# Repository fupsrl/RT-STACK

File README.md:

# RT-STACK

**RT-STACK is an open-source, real-time engine-control platform for experimental, motorsport, and bench-development applications.** It combines a deterministic STM32G4 real-time controller with the option to add a Raspberry Pi or another high-level computer for advanced control, data handling, and calibration workflows.

The hardware is deliberately ambitious—twelve injector channels, twelve ignition channels, trigger inputs, lambda interfaces, CAN, and a standard ECU connector—while the checked-in firmware is a transparent, configurable reference implementation. Start on the bench, understand every signal, then adapt the engine, trigger, and output configuration for your application.

> [!WARNING]
> RT-STACK is an engineering/development project. It is not certified, not road-legal, and is supplied without warranty. Do not connect coils, injectors, fuel pumps, or a running engine until you have independently validated the wiring, trigger decode, outputs, and failsafe behaviour on a safe bench setup.

## Why RT-STACK?

- **Real-time where it matters** — the STM32G474 handles time-critical trigger capture, injection and ignition scheduling.
- **Headroom where it helps** — a companion SBC can run high-level logic, graphical control models, logging, and calibration tooling without putting hard real-time output timing at risk.
- **Engine-agnostic by design** — the platform can be adapted for 2-stroke, 4-stroke, Wankel, Diesel, naturally aspirated, or forced-induction projects.
- **A serious hardware base** — the board is designed for high-channel-count PFI/GDI injection, inductive ignition, trigger sensing, lambda control, and general-purpose outputs.
- **Open calibration path** — the wider FUPSRL toolchain supports CAN/XCP workflows and A2L/HEX artefacts for tools such as ETAS INCA and Vector CANape. The current firmware also includes a 500 kbit/s classic-CAN status message and its DBC.

## Architecture

```text
Crank / cam / sensors
        │
        ▼
STM32G474 real-time layer ──► injector, ignition and I/O drivers
        │                         ▲
        ├── CAN telemetry          │ deterministic time-critical control
        ▼                         │
Optional SBC / high-level layer ──┘
  control logic · logging · calibration · user interface
```

The STM32 is the safety- and timing-critical controller. A companion computer is optional and should be treated as a supervisory layer, not as a replacement for deterministic output control.

## Hardware capabilities

| Area | Capability |
| --- | --- |
| Fuel | 12 injector drivers, intended for general-purpose GDI or PFI use; high-voltage DC/DC injector drive and current sensing |
| Ignition | 12 inductive-spark channels |
| Position sensing | 9 general-purpose trigger interfaces for crank, cam, turbo speed, or other timing inputs |
| Lambda | 2 × CJ125 lambda-controller interfaces |
| Outputs | 12 general-purpose outputs with selectable push/pull behaviour |
| Communications | FDCAN-capable MCU; the checked-in project configures classic CAN at 500 kbit/s and includes two UARTs |
| Processor | STM32G474VETx, with analogue comparators and DAC thresholds for injector-drive control |
| Integration | 186-pin standard ECU connector; designed to stack with a Raspberry Pi breakout board for high-level control |

Selected devices include the STM32G474VETx, ACS722 current sensing, CJ125 lambda interfaces, IR2101/TC4427 gate drivers, RGPR30BM40 ignition IGBTs, and IFX007TAUMA1 push/pull drivers. Consult the KiCad design and BOM before making any electrical decision; this README is an overview, not a wiring specification.

## Firmware: current scope

The firmware project lives in [`SW/RT_STACK_V2`](SW/RT_STACK_V2) and is an STM32CubeIDE / STM32CubeMX project. It provides a clear reference structure rather than a sealed, generic binary:

- **Trigger capture and decoding** — trigger edges are timestamped with the DWT cycle counter. The included decoder is configured for a 60-2 crank wheel, optional cam recognition, and 0–720° phase fusion.
- **Engine configuration** — cylinder count, firing order, ignition/injector channel mapping, dwell limit, boost time, and comparator thresholds are centralised in [`engine_config.h`](SW/RT_STACK_V2/Core/Inc/engine_config.h).
- **Trigger configuration** — crank-wheel and cam-pattern settings are centralised in [`trigger_decoder_config.h`](SW/RT_STACK_V2/Core/Inc/trigger_decoder_config.h).
- **Output scheduling** — [`spark.c`](SW/RT_STACK_V2/Core/Src/spark.c) and [`injection.c`](SW/RT_STACK_V2/Core/Src/injection.c) schedule the configured engine channels.
- **Telemetry** — `RT_Status` is sent as an 8-byte classic-CAN frame at identifier `0x100` every 10 ms; [`RT_STACK_V2.dbc`](SW/RT_STACK_V2/RT_STACK_V2.dbc) describes that message.

The committed engine calibration is an **inline-four example** (firing order `1-3-4-2`) and is not a V12 calibration. V12 readiness describes the available I/O architecture; you must supply a correctly validated configuration for every target engine.

## Quick start — safe development workflow

1. Clone the repository and open [`SW/RT_STACK_V2`](SW/RT_STACK_V2) in STM32CubeIDE. The `.ioc` file retains the CubeMX peripheral configuration.
2. Read `engine_config.h` and `trigger_decoder_config.h` before connecting any engine hardware. Configure only a bench-known target first.
3. Build the **Debug** configuration and flash through a correctly wired ST-LINK connection.
4. With injectors and coils disconnected, verify power rails, CAN traffic, trigger-edge polarity, decoded crank angle, RPM, and cam phase using instruments you trust.
5. Validate each output with suitable loads or test fixtures. Add engine actuation only after the whole chain has been checked.

For a guided explanation of the architecture, firmware configuration, CAN telemetry, calibration direction, and bench validation, read the [RT-STACK documentation](https://fupsrl.com/docs/rt-stack-documentation-v1/).

## Repository layout

| Path | Contents |
| --- | --- |
| [`HW`](HW) | KiCad hardware design files |
| [`FAB`](FAB) | Fabrication/manufacturing material |
| [`SW/RT_STACK_V2`](SW/RT_STACK_V2) | STM32CubeIDE firmware project, DBC, source, and CubeMX configuration |
| [`assets`](assets) | Repository artwork, including this README banner |

## Hardware preview

## Calibration and companion tools

RT-STACK is designed to sit within a broader open tooling workflow. The [CM-STACK Simulink Compiler](https://github.com/fupsrl/CM-STACK-Simulink-Compiler) creates deployable generic-Linux applications and calibration artefacts, while [INCAZ](https://github.com/fupsrl/INCAZ) is a lightweight measurement, calibration, and flash client. Treat each integration as a separately validated engineering step.

## Contributing and support

Issues and pull requests are welcome, especially reproducible trigger-decoder tests, documentation corrections, and validated engine configurations. Please include the RT-STACK revision, firmware commit, engine/trigger setup, power supply conditions, and the measurements or logs that demonstrate the behaviour.

## License

RT-STACK is licensed under [Creative Commons Attribution-NonCommercial 4.0 International](LICENSE.txt). Attribution is required and commercial use is not permitted.

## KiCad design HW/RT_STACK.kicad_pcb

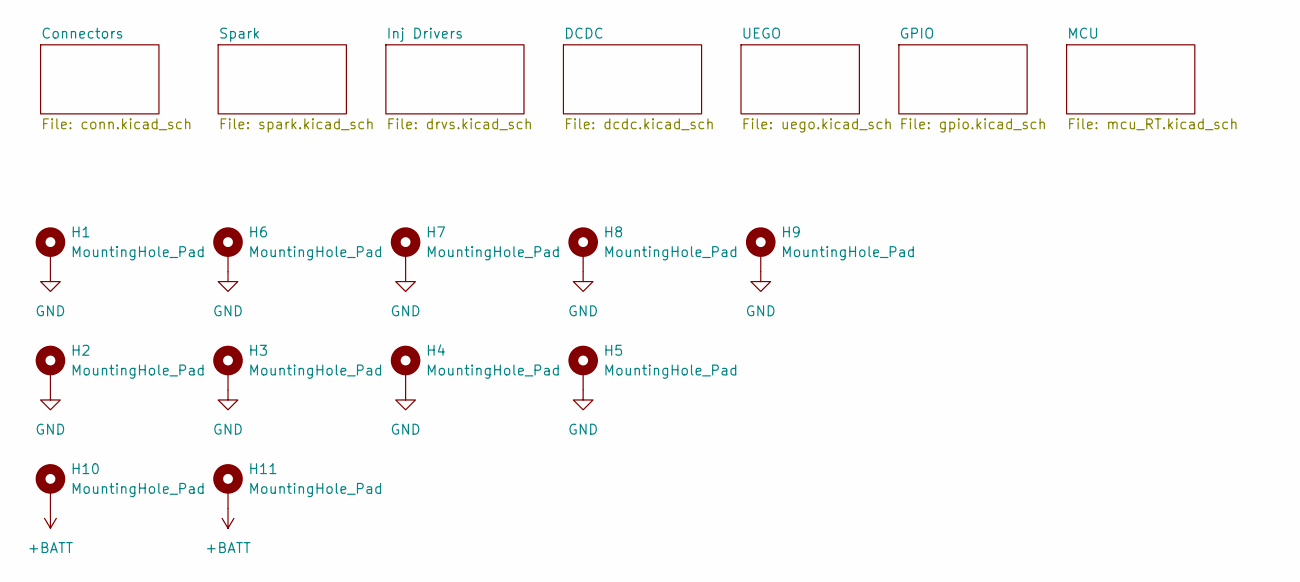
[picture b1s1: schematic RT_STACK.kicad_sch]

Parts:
H1, H6, H7, H8, H9, H10, H11: MountingHole_Pad; MountingHole_2.2mm_M2_DIN965_Pad_TopBottom
H2, H3, H4, H5: MountingHole_Pad; MountingHole_3.2mm_M3_DIN965_Pad_TopBottom

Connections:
+BATT: H10.1, H11.1; also elsewhere on the board
GND: H1.1, H2.1, H3.1, H4.1, H5.1, H6.1, H7.1, H8.1, H9.1; also elsewhere on the board

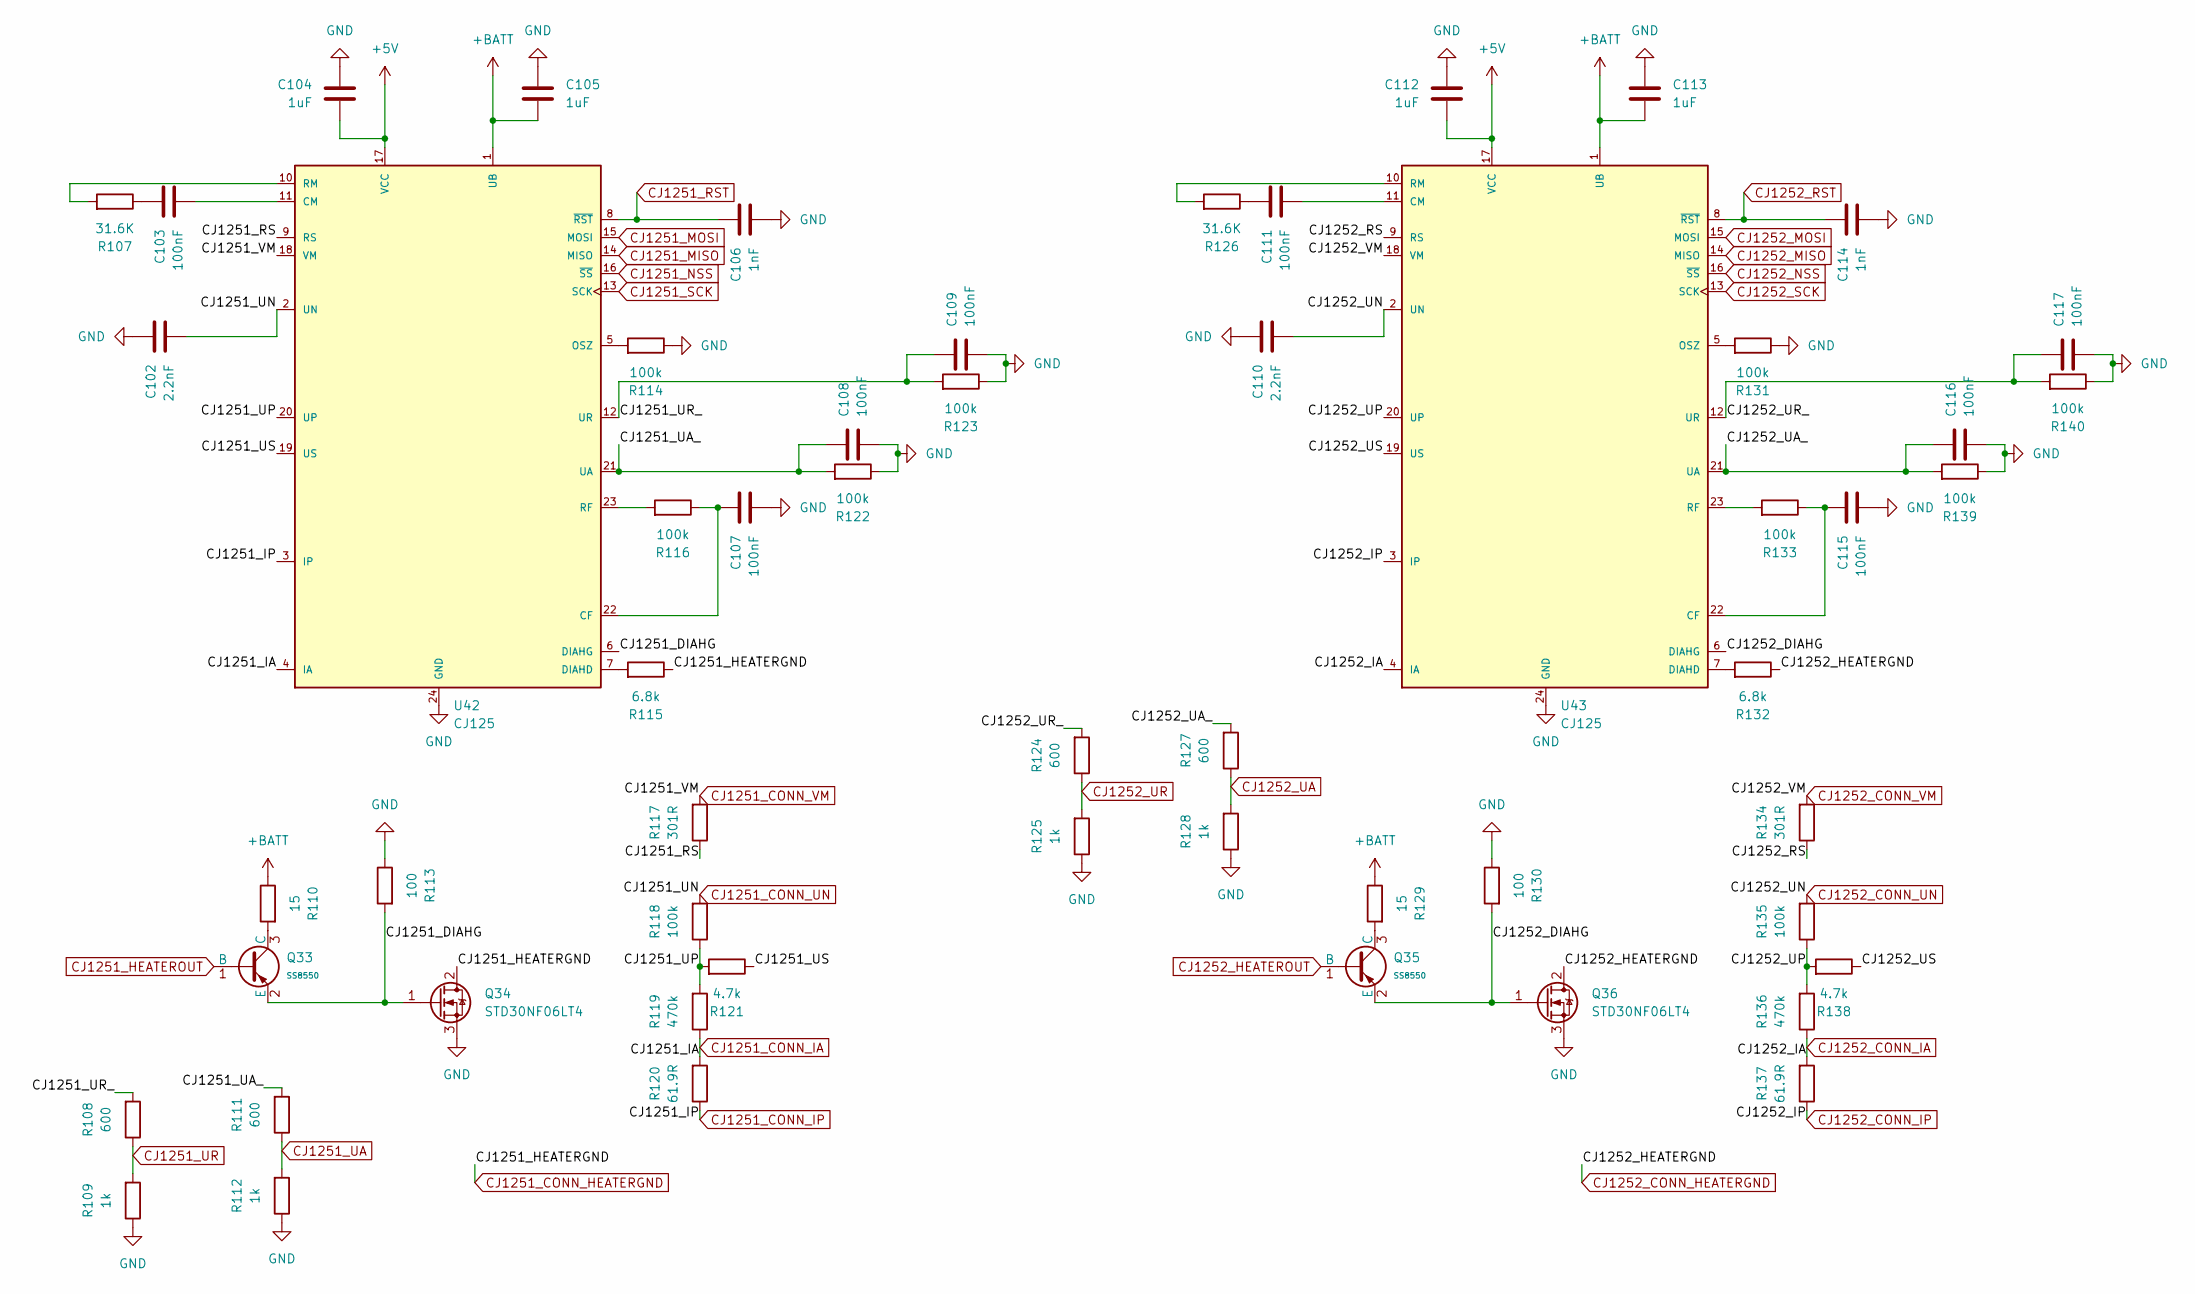
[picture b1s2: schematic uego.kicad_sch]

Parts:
C102, C110: 2.2nF; C_0402_1005Metric
C103, C107, C108, C109, C111, C115, C116, C117: 100nF; C_0402_1005Metric
C104, C105, C112, C113: 1uF; C_0402_1005Metric
C106, C114: 1nF; C_0402_1005Metric
Q33, Q35: SS8550; Q_SOT-23; Part SS8550; LCSC C7420371
Q34, Q36: STD30NF06LT4; TO-252-2
R107, R126: 31.6K; R_0402_1005Metric
R108, R111, R124, R127: 600; R_0402_1005Metric
R109, R112, R125, R128: 1k; R_0402_1005Metric
R110, R129: 15; R_0402_1005Metric
R113, R130: 100; R_0402_1005Metric
R114, R116, R118, R122, R123, R131, R133, R135, R139, R140: 100k; R_0402_1005Metric
R115, R132: 6.8k; R_0402_1005Metric
R117, R134: 301R; R_0402_1005Metric
R119, R136: 470k; R_0402_1005Metric
R120, R137: 61.9R; R_0402_1005Metric
R121, R138: 4.7k; R_0402_1005Metric
U42, U43: CJ125; SO24W

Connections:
+5V: C104.2, C112.2, U42.17 (VCC), U43.17 (VCC); also elsewhere on the board
+BATT: C105.2, C113.2, R110.1, R129.1, U42.1 (UB), U43.1 (UB); also elsewhere on the board
/UEGO/CJ1251_DIAHG: Q33.2 (E), Q34.1 (G), R113.2, U42.6 (DIAHG)
/UEGO/CJ1251_RS: R117.1, U42.9 (RS)
/UEGO/CJ1251_UA_: C108.1, R111.2, R122.2, U42.21 (UA)
/UEGO/CJ1251_UP: R118.1, R119.2, R121.2, U42.20 (UP)
/UEGO/CJ1251_UR_: C109.1, R108.2, R123.2, U42.12 (UR)
/UEGO/CJ1251_US: R121.1, U42.19 (US)
/UEGO/CJ1252_DIAHG: Q35.2 (E), Q36.1 (G), R130.2, U43.6 (DIAHG)
/UEGO/CJ1252_RS: R134.1, U43.9 (RS)
/UEGO/CJ1252_UA_: C116.1, R127.2, R139.2, U43.21 (UA)
/UEGO/CJ1252_UP: R135.1, R136.2, R138.2, U43.20 (UP)
/UEGO/CJ1252_UR_: C117.1, R124.2, R140.2, U43.12 (UR)
/UEGO/CJ1252_US: R138.1, U43.19 (US)
CJ1251_CONN_HEATERGND: Q34.2 (D), R115.1; also elsewhere on the board
CJ1251_CONN_IA: R119.1, R120.2, U42.4 (IA); also elsewhere on the board
CJ1251_CONN_IP: R120.1, U42.3 (IP); also elsewhere on the board
CJ1251_CONN_UN: C102.2, R118.2, U42.2 (UN); also elsewhere on the board
CJ1251_CONN_VM: R117.2, U42.18 (VM); also elsewhere on the board
CJ1251_HEATEROUT: Q33.1 (B); also elsewhere on the board
CJ1251_MISO: U42.14 (MISO); also elsewhere on the board
CJ1251_MOSI: U42.15 (MOSI); also elsewhere on the board
CJ1251_NSS: U42.16 (~SS); also elsewhere on the board
CJ1251_RST: C106.1, U42.8 (~RST)
CJ1251_SCK: U42.13 (SCK); also elsewhere on the board
CJ1251_UA: R111.1, R112.2; also elsewhere on the board
CJ1251_UR: R108.1, R109.2; also elsewhere on the board
CJ1252_CONN_HEATERGND: Q36.2 (D), R132.1; also elsewhere on the board
CJ1252_CONN_IA: R136.1, R137.2, U43.4 (IA); also elsewhere on the board
CJ1252_CONN_IP: R137.1, U43.3 (IP); also elsewhere on the board
CJ1252_CONN_UN: C110.2, R135.2, U43.2 (UN); also elsewhere on the board
CJ1252_CONN_VM: R134.2, U43.18 (VM); also elsewhere on the board
CJ1252_HEATEROUT: Q35.1 (B); also elsewhere on the board
CJ1252_MISO: U43.14 (MISO); also elsewhere on the board
CJ1252_MOSI: U43.15 (MOSI); also elsewhere on the board
CJ1252_NSS: U43.16 (~SS); also elsewhere on the board
CJ1252_RST: C114.1, U43.8 (~RST)
CJ1252_SCK: U43.13 (SCK); also elsewhere on the board
CJ1252_UA: R127.1, R128.2; also elsewhere on the board
CJ1252_UR: R124.1, R125.2; also elsewhere on the board
GND: C102.1, C104.1, C105.1, C106.2, C107.2, C108.2, C109.2, C110.1, C112.1, C113.1, C114.2, C115.2, C116.2, C117.2, Q34.3 (S), Q36.3 (S), R109.1, R112.1, R113.1, R114.1, R122.1, R123.1, R125.1, R128.1, R130.1, R131.1, R139.1, R140.1, U42.24 (GND), U43.24 (GND); also elsewhere on the board
unnamed: C103.1, R107.1
unnamed: C111.1, R126.1
unnamed: Q33.3 (C), R110.2
unnamed: Q35.3 (C), R129.2
unnamed: C107.1, R116.1, U42.22 (CF)
unnamed: C103.2, U42.11 (CM)
unnamed: R115.2, U42.7 (DIAHD)
unnamed: R114.2, U42.5 (OSZ)
unnamed: R116.2, U42.23 (RF)
unnamed: R107.2, U42.10 (RM)
unnamed: C115.1, R133.1, U43.22 (CF)
unnamed: C111.2, U43.11 (CM)
unnamed: R132.2, U43.7 (DIAHD)
unnamed: R131.2, U43.5 (OSZ)
unnamed: R133.2, U43.23 (RF)
unnamed: R126.2, U43.10 (RM)

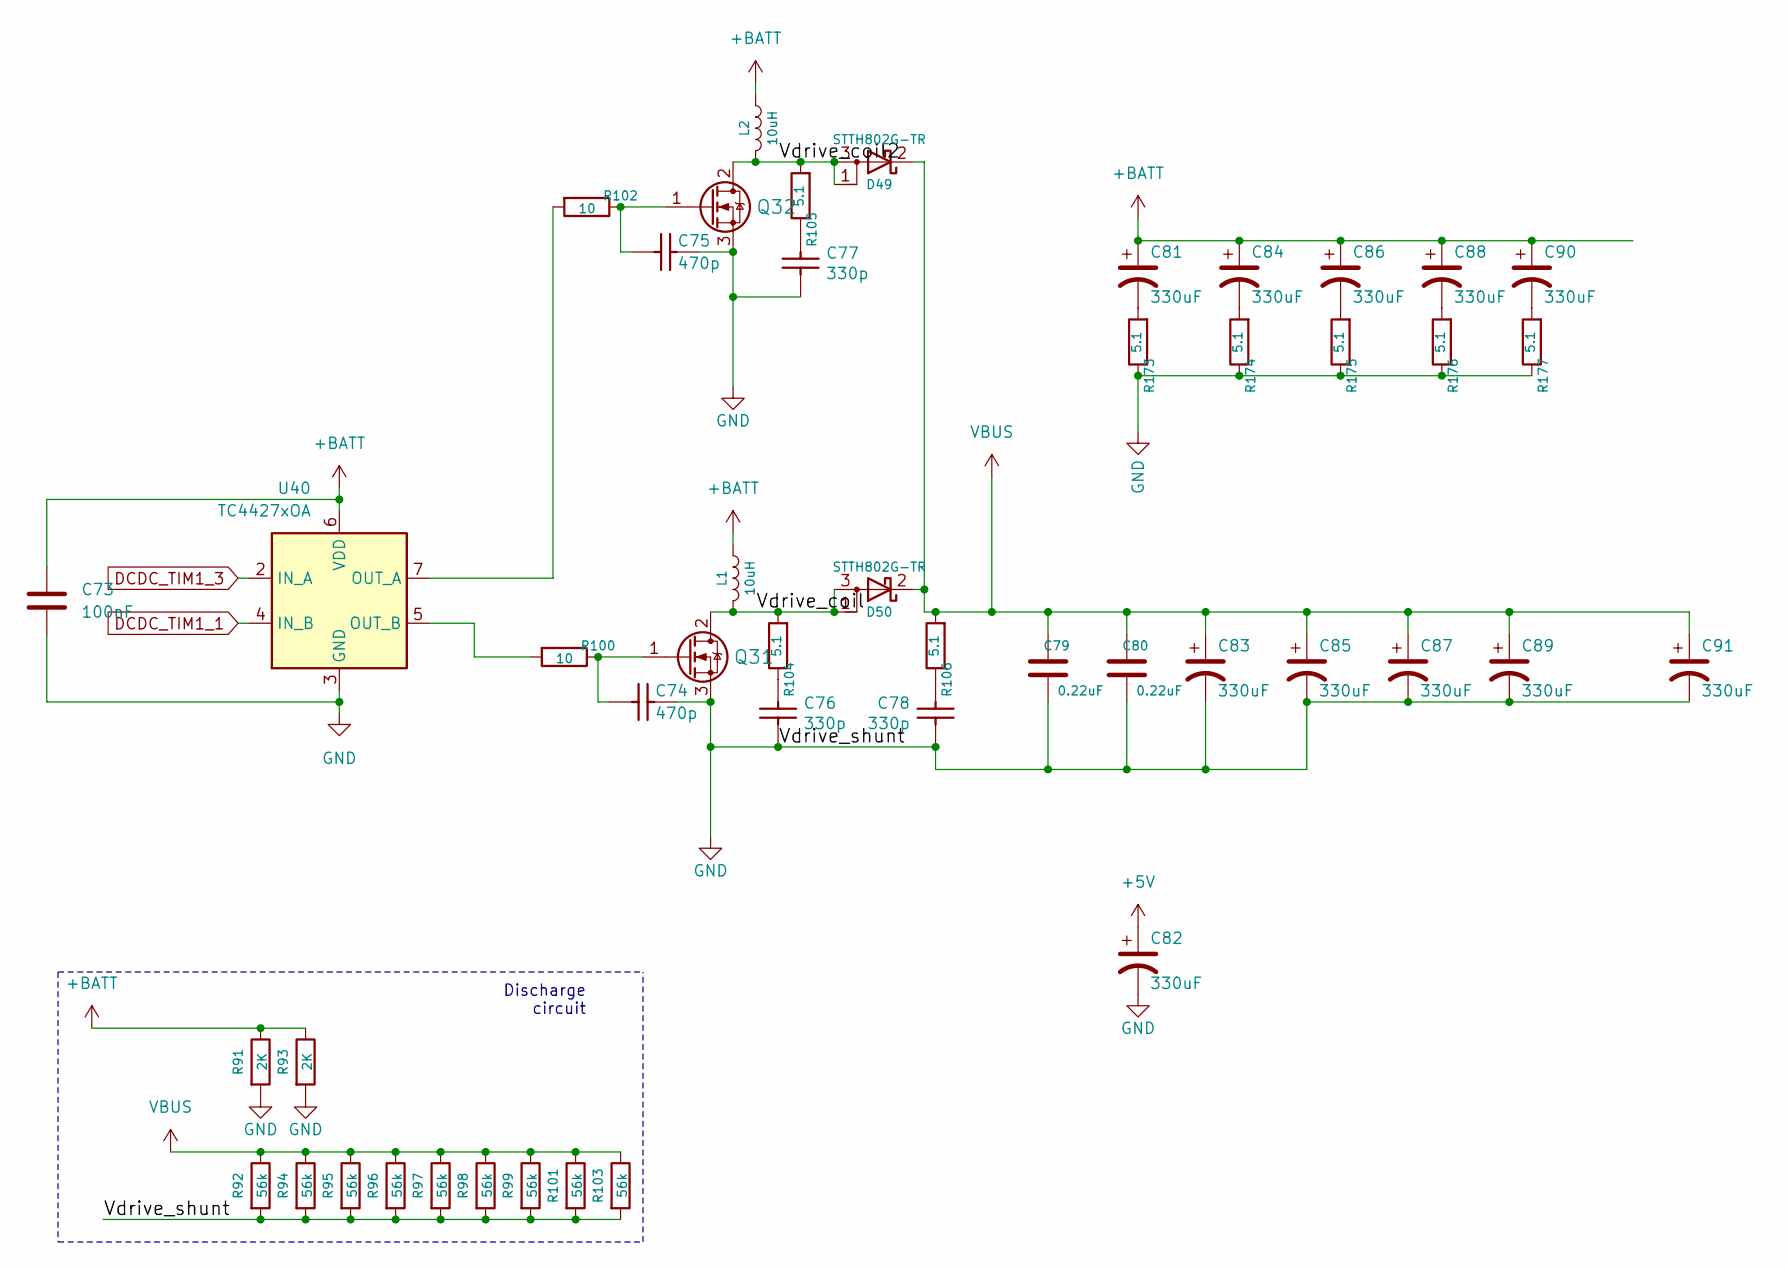
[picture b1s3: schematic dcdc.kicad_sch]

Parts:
C73: 100nF; C_0402_1005Metric; JLC C77020
C74, C75: 470p; C_0603_1608Metric; LCSC C326973
C76, C77, C78: 330p; C_0603_1608Metric; LCSC C576850
C79, C80: 0.22uF; C_0805_2012Metric; LCSC C513710
C81, C82, C83, C84, C85, C86, C87, C88, C89, C90, C91: 330uF; CP_Radial_D12.5mm_P5.00mm
D49, D50: STTH802G-TR; TO-263-2; LCSC C181034
L1, L2: 10uH; L_Vishay_IHLP-6767; LCSC C237980
Q31, Q32: BUK9230-100B; TO-252-2; LCSC C89735
R91, R93: 2K; R_1206_3216Metric; LCSC C17944
R92, R94, R95, R96, R97, R98, R99, R101, R103: 56k; R_0805_2012Metric; LCSC C17756
R100, R102: 10; R_0603_1608Metric; LCSC C60485
R104, R105, R106, R173, R174, R175, R176, R177: 5.1; R_0603_1608Metric; LCSC C25197
U40: TC4427xOA; SOIC-8_3.9x4.9mm_P1.27mm; JLC C640788

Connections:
+5V: C82.1; also elsewhere on the board
+BATT: C73.1, C81.1, C84.1, C86.1, C88.1, C90.1, L1.1, L2.1, R91.1, R93.1, U40.6 (VDD); also elsewhere on the board
/DCDC/Vdrive_coil: D50.1 (A), D50.3 (A), L1.2, Q31.2 (D), R104.2
/DCDC/Vdrive_coil2: D49.1 (A), D49.3 (A), L2.2, Q32.2 (D), R105.2
DCDC_TIM1_1: U40.4 (IN_B); also elsewhere on the board
DCDC_TIM1_3: U40.2 (IN_A); also elsewhere on the board
GND: C73.2, C74.1, C75.1, C76.1, C77.1, C78.1, C79.2, C80.2, C82.2, C83.2, C85.2, C87.2, C89.2, C91.2, Q31.3 (S), Q32.3 (S), R91.2, R92.2, R93.2, R94.2, R95.2, R96.2, R97.2, R98.2, R99.2, R101.2, R103.2, R173.1, R174.1, R175.1, R176.1, R177.1, U40.3 (GND); also elsewhere on the board
unnamed: C76.2, R104.1
unnamed: C77.2, R105.1
unnamed: C78.2, R106.1
unnamed: C81.2, R173.2
unnamed: C84.2, R174.2
unnamed: C86.2, R175.2
unnamed: C88.2, R176.2
unnamed: C90.2, R177.2
unnamed: C74.2, Q31.1 (G), R100.1
unnamed: C75.2, Q32.1 (G), R102.1
unnamed: R102.2, U40.7 (OUT_A)
unnamed: R100.2, U40.5 (OUT_B)
VBUS: C79.1, C80.1, C83.1, C85.1, C87.1, C89.1, C91.1, D49.2 (K), D50.2 (K), R92.1, R94.1, R95.1, R96.1, R97.1, R98.1, R99.1, R101.1, R103.1, R106.2; also elsewhere on the board

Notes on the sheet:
Discharge circuit

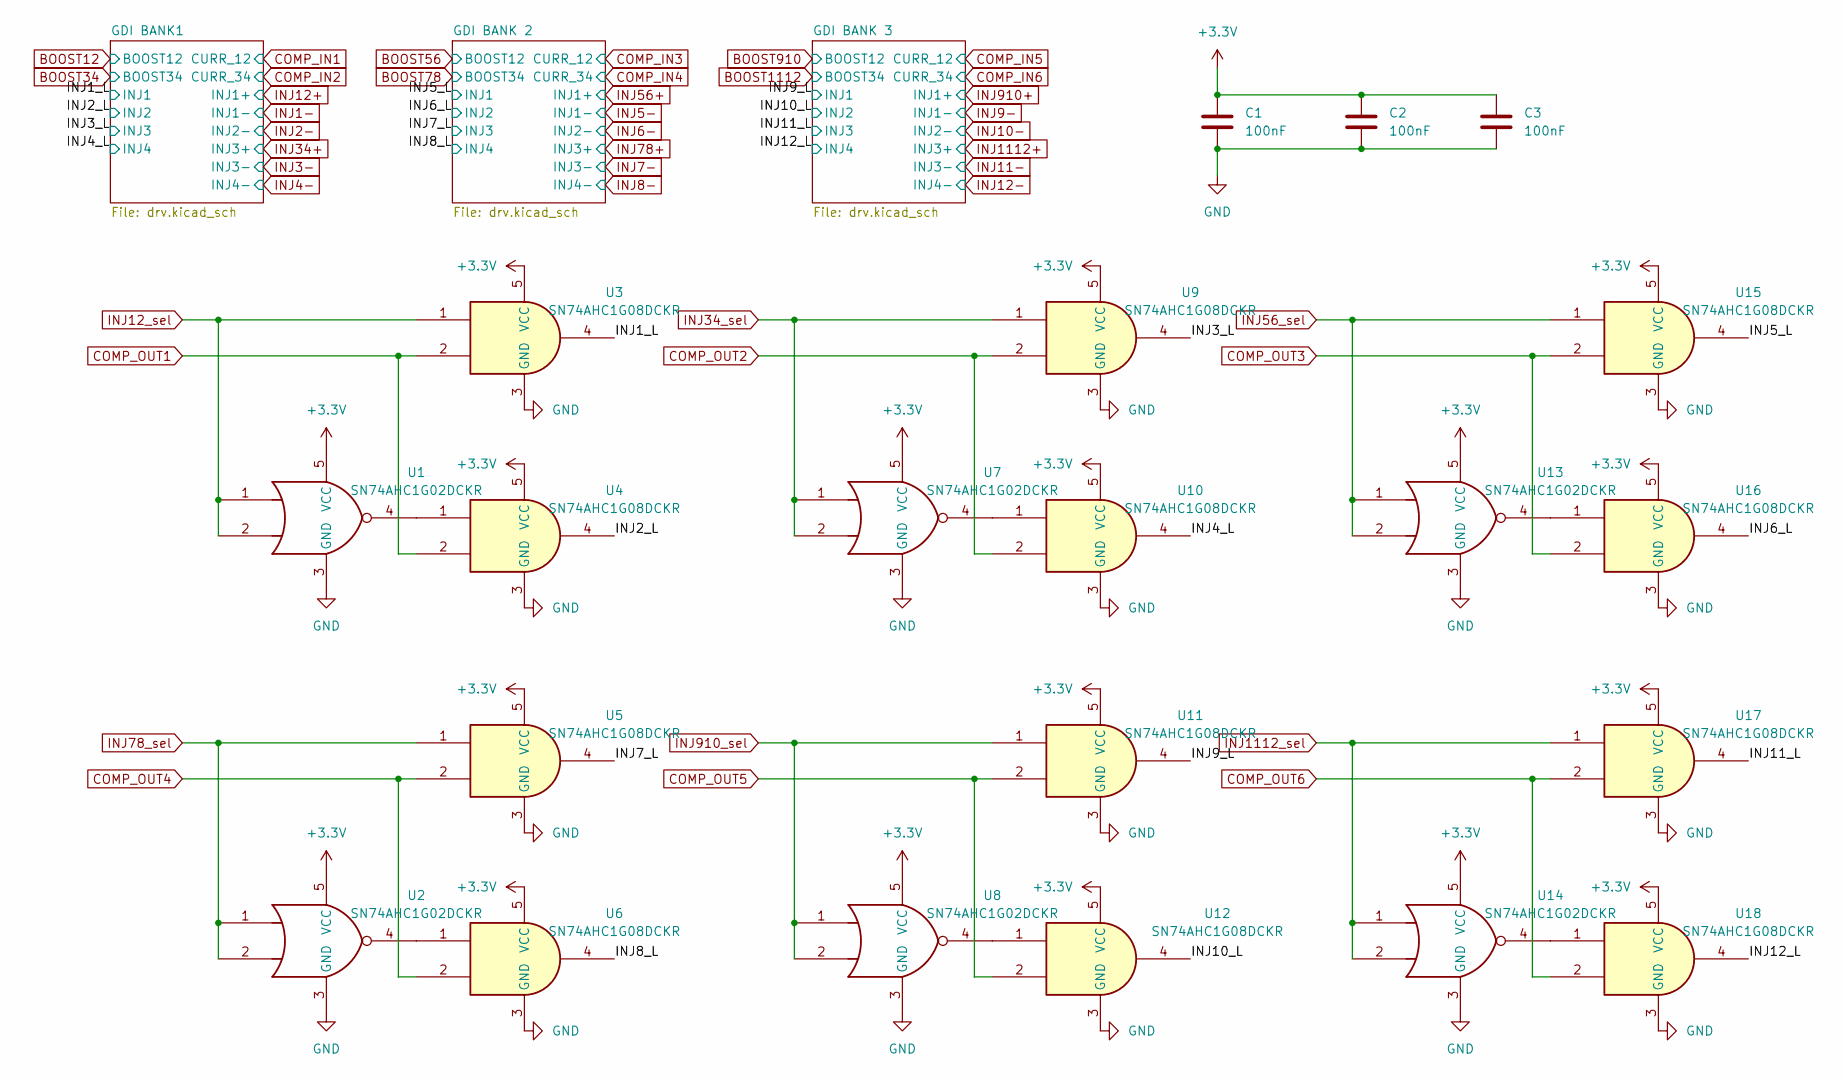
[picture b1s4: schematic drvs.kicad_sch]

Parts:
C1, C2, C3: 100nF; C_0402_1005Metric
U1, U2, U7, U8, U13, U14: SN74AHC1G02DCKR; SOT-353_SC-70-5; JLC C7464
U3, U4, U5, U6, U9, U10, U11, U12, U15, U16, U17, U18: SN74AHC1G08DCKR; SOT-353_SC-70-5; JLC C122838

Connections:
+3.3V: C1.1, C2.1, C3.1, U1.5 (VCC), U2.5 (VCC), U3.5 (VCC), U4.5 (VCC), U5.5 (VCC), U6.5 (VCC), U7.5 (VCC), U8.5 (VCC), U9.5 (VCC), U10.5 (VCC), U11.5 (VCC), U12.5 (VCC), U13.5 (VCC), U14.5 (VCC), U15.5 (VCC), U16.5 (VCC), U17.5 (VCC), U18.5 (VCC); also elsewhere on the board
/Inj Drivers/INJ1_L: U3.4; also elsewhere on the board
/Inj Drivers/INJ2_L: U4.4; also elsewhere on the board
/Inj Drivers/INJ3_L: U9.4; also elsewhere on the board
/Inj Drivers/INJ4_L: U10.4; also elsewhere on the board
/Inj Drivers/INJ5_L: U15.4; also elsewhere on the board
/Inj Drivers/INJ6_L: U16.4; also elsewhere on the board
/Inj Drivers/INJ7_L: U5.4; also elsewhere on the board
/Inj Drivers/INJ8_L: U6.4; also elsewhere on the board
/Inj Drivers/INJ9_L: U11.4; also elsewhere on the board
/Inj Drivers/INJ10_L: U12.4; also elsewhere on the board
/Inj Drivers/INJ11_L: U17.4; also elsewhere on the board
/Inj Drivers/INJ12_L: U18.4; also elsewhere on the board
COMP_OUT1: U3.2, U4.2; also elsewhere on the board
COMP_OUT2: U9.2, U10.2; also elsewhere on the board
COMP_OUT3: U15.2, U16.2; also elsewhere on the board
COMP_OUT4: U5.2, U6.2; also elsewhere on the board
COMP_OUT5: U11.2, U12.2; also elsewhere on the board
COMP_OUT6: U17.2, U18.2; also elsewhere on the board
GND: C1.2, C2.2, C3.2, U1.3 (GND), U2.3 (GND), U3.3 (GND), U4.3 (GND), U5.3 (GND), U6.3 (GND), U7.3 (GND), U8.3 (GND), U9.3 (GND), U10.3 (GND), U11.3 (GND), U12.3 (GND), U13.3 (GND), U14.3 (GND), U15.3 (GND), U16.3 (GND), U17.3 (GND), U18.3 (GND); also elsewhere on the board
INJ12_sel: U1.1, U1.2, U3.1; also elsewhere on the board
INJ34_sel: U7.1, U7.2, U9.1; also elsewhere on the board
INJ56_sel: U13.1, U13.2, U15.1; also elsewhere on the board
INJ78_sel: U2.1, U2.2, U5.1; also elsewhere on the board
INJ910_sel: U8.1, U8.2, U11.1; also elsewhere on the board
INJ1112_sel: U14.1, U14.2, U17.1; also elsewhere on the board
unnamed: U1.4, U4.1
unnamed: U2.4, U6.1
unnamed: U7.4, U10.1
unnamed: U8.4, U12.1
unnamed: U13.4, U16.1
unnamed: U14.4, U18.1

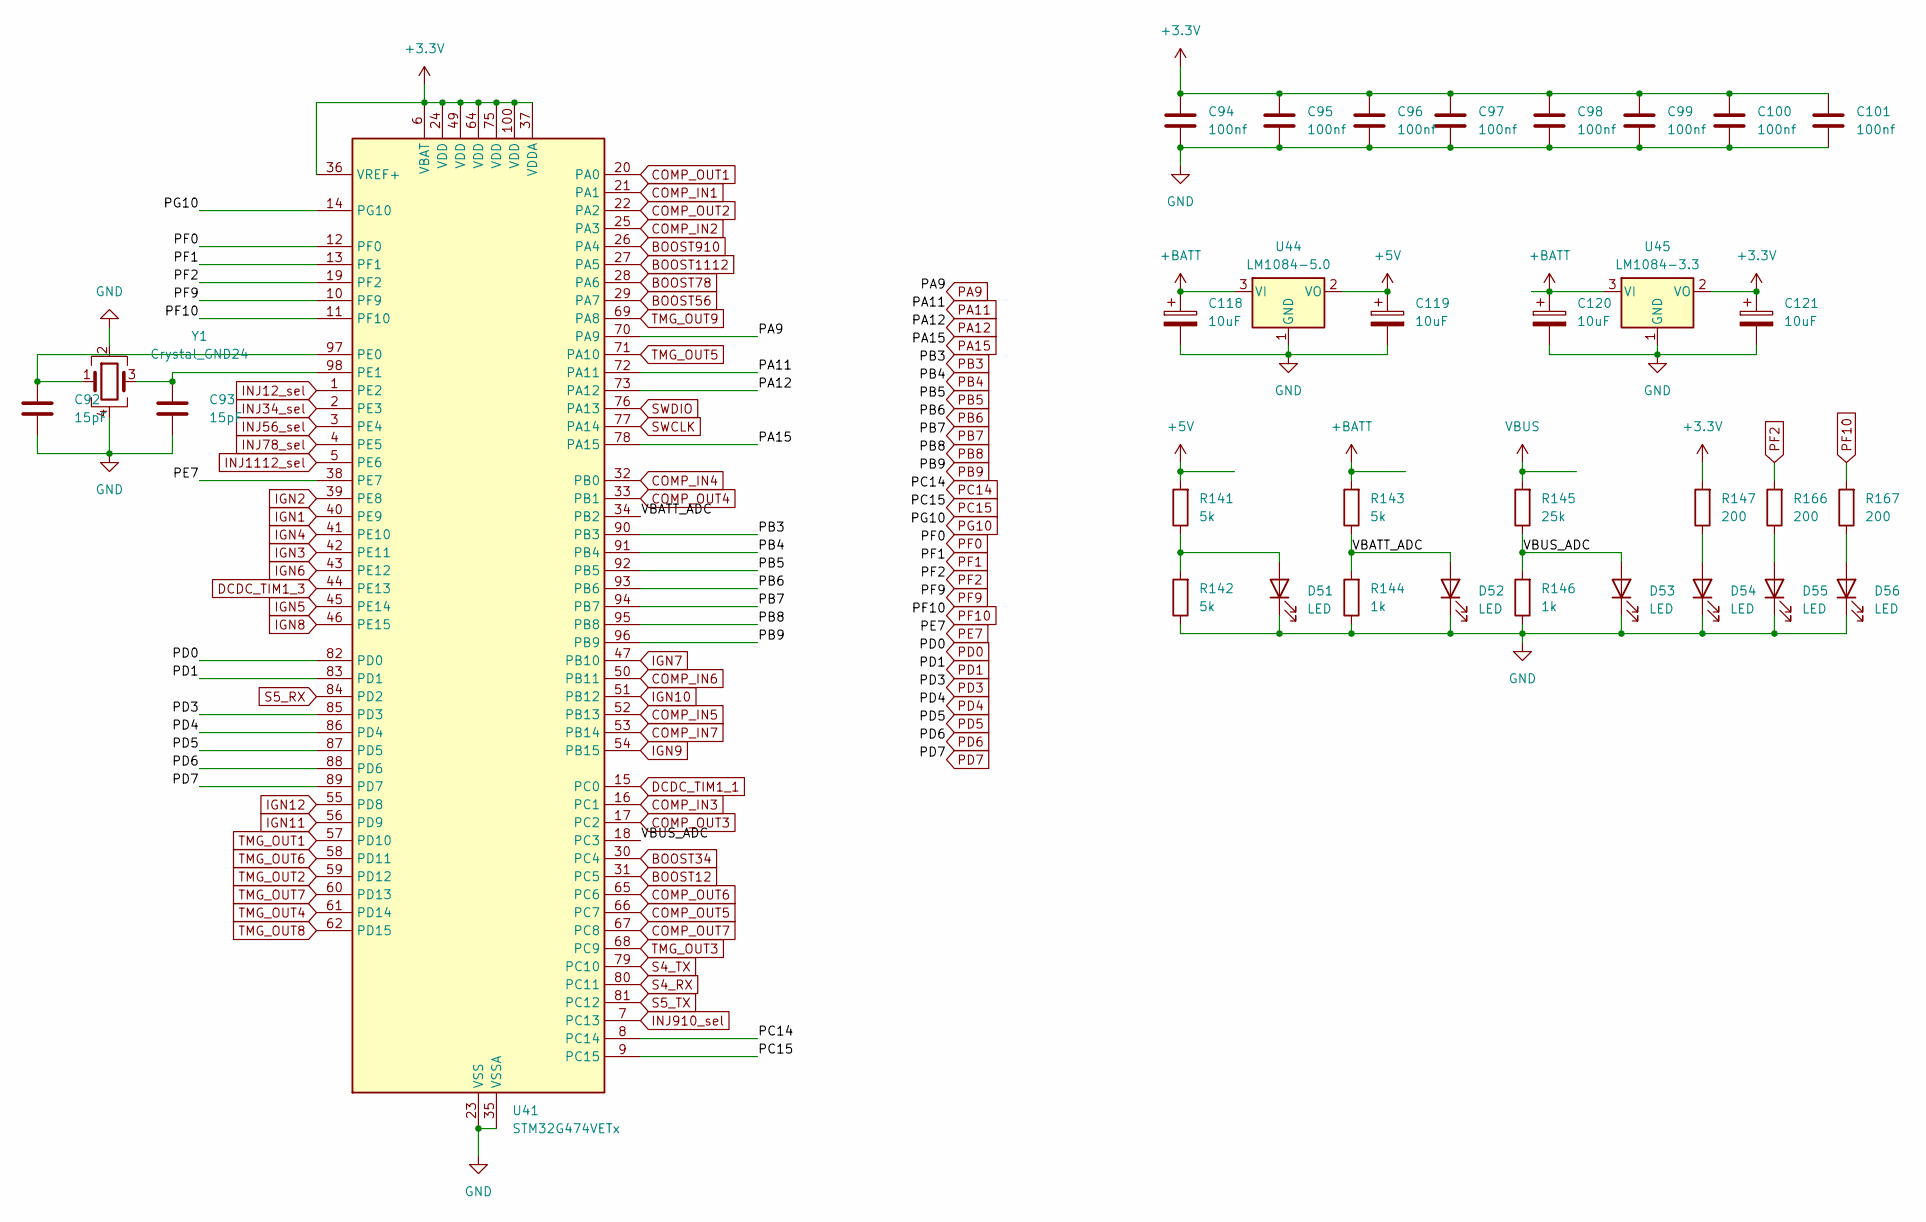
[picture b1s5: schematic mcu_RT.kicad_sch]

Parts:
C92, C93: 15pF; C_0402_1005Metric
C94, C95, C96, C97, C98, C99, C100, C101: 100nf; C_0402_1005Metric
C118, C119, C120, C121: 10uF; CP_Elec_5x4.5
D51, D52, D53, D54, D55, D56: LED; LED_0402_1005Metric
R141, R142, R143: 5k; R_0402_1005Metric
R144, R146: 1k; R_0402_1005Metric
R145: 25k; R_0402_1005Metric
R147, R166, R167: 200; R_0402_1005Metric
U41: STM32G474VETx; LQFP-100_14x14mm_P0.5mm
U44: LM1084-5.0; TO-263-3_TabPin2
U45: LM1084-3.3; TO-263-3_TabPin2
Y1: Crystal_GND24; Crystal_SMD_2016-4Pin_2.0x1.6mm

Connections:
+3.3V: C94.1, C95.1, C96.1, C97.1, C98.1, C99.1, C100.1, C101.1, C121.1, R147.2, U41.6 (VBAT), U41.24 (VDD), U41.36 (VREF+), U41.37 (VDDA), U41.49 (VDD), U41.64 (VDD), U41.75 (VDD), U41.100 (VDD), U45.2 (VO); also elsewhere on the board
+5V: C119.1, R141.2, U44.2 (VO); also elsewhere on the board
+BATT: C118.1, C120.1, R143.2, U44.3 (VI), U45.3 (VI); also elsewhere on the board
/MCU/CAN_RX: U41.73 (PA12); also elsewhere on the board
/MCU/CAN_TX: U41.72 (PA11); also elsewhere on the board
/MCU/VBATT_ADC: D52.2 (A), R143.1, R144.2, U41.34 (PB2)
/MCU/VBUS_ADC: D53.2 (A), R145.1, R146.2, U41.18 (PC3)
BOOST12: U41.31 (PC5); also elsewhere on the board
BOOST34: U41.30 (PC4); also elsewhere on the board
BOOST56: U41.29 (PA7); also elsewhere on the board
BOOST78: U41.28 (PA6); also elsewhere on the board
BOOST910: U41.26 (PA4); also elsewhere on the board
BOOST1112: U41.27 (PA5); also elsewhere on the board
COMP_IN1: U41.21 (PA1); also elsewhere on the board
COMP_IN2: U41.25 (PA3); also elsewhere on the board
COMP_IN3: U41.16 (PC1); also elsewhere on the board
COMP_IN4: U41.32 (PB0); also elsewhere on the board
COMP_IN5: U41.52 (PB13); also elsewhere on the board
COMP_IN6: U41.50 (PB11); also elsewhere on the board
COMP_IN7: U41.53 (PB14); also elsewhere on the board
COMP_OUT1: U41.20 (PA0); also elsewhere on the board
COMP_OUT2: U41.22 (PA2); also elsewhere on the board
COMP_OUT3: U41.17 (PC2); also elsewhere on the board
COMP_OUT4: U41.33 (PB1); also elsewhere on the board
COMP_OUT5: U41.66 (PC7); also elsewhere on the board
COMP_OUT6: U41.65 (PC6); also elsewhere on the board
COMP_OUT7: U41.67 (PC8); also elsewhere on the board
DCDC_TIM1_1: U41.15 (PC0); also elsewhere on the board
DCDC_TIM1_3: U41.44 (PE13); also elsewhere on the board
GND: C92.2, C93.2, C94.2, C95.2, C96.2, C97.2, C98.2, C99.2, C100.2, C101.2, C118.2, C119.2, C120.2, C121.2, D51.1 (K), D52.1 (K), D53.1 (K), D54.1 (K), D55.1 (K), D56.1 (K), R142.1, R144.1, R146.1, U41.23 (VSS), U41.35 (VSSA), U41.48 (VSS), U41.63 (VSS), U41.74 (VSS), U41.99 (VSS), U44.1 (GND), U45.1 (GND), Y1.2, Y1.4; also elsewhere on the board
IGN1: U41.40 (PE9); also elsewhere on the board
IGN2: U41.39 (PE8); also elsewhere on the board
IGN3: U41.42 (PE11); also elsewhere on the board
IGN4: U41.41 (PE10); also elsewhere on the board
IGN5: U41.45 (PE14); also elsewhere on the board
IGN6: U41.43 (PE12); also elsewhere on the board
IGN7: U41.47 (PB10); also elsewhere on the board
IGN8: U41.46 (PE15); also elsewhere on the board
IGN9: U41.54 (PB15); also elsewhere on the board
IGN10: U41.51 (PB12); also elsewhere on the board
IGN11: U41.56 (PD9); also elsewhere on the board
IGN12: U41.55 (PD8); also elsewhere on the board
INJ12_sel: U41.1 (PE2); also elsewhere on the board
INJ34_sel: U41.2 (PE3); also elsewhere on the board
INJ56_sel: U41.3 (PE4); also elsewhere on the board
INJ78_sel: U41.4 (PE5); also elsewhere on the board
INJ910_sel: U41.7 (PC13); also elsewhere on the board
INJ1112_sel: U41.5 (PE6); also elsewhere on the board
unnamed: D51.2 (A), R141.1, R142.2
unnamed: D54.2 (A), R147.1
unnamed: D55.2 (A), R166.1
unnamed: D56.2 (A), R167.1
unnamed: C92.1, U41.97 (PE0), Y1.1
unnamed: C93.1, U41.98 (PE1), Y1.3
PA9: U41.70 (PA9); also elsewhere on the board
PA15: U41.78 (PA15); also elsewhere on the board
PB3: U41.90 (PB3); also elsewhere on the board
PB4: U41.91 (PB4); also elsewhere on the board
PB5: U41.92 (PB5); also elsewhere on the board
PB6: U41.93 (PB6); also elsewhere on the board
PB7: U41.94 (PB7); also elsewhere on the board
PB8: U41.95 (PB8); also elsewhere on the board
PB9: U41.96 (PB9); also elsewhere on the board
PC14: U41.8 (PC14); also elsewhere on the board
PC15: U41.9 (PC15); also elsewhere on the board
PD0: U41.82 (PD0); also elsewhere on the board
PD1: U41.83 (PD1); also elsewhere on the board
PD3: U41.85 (PD3); also elsewhere on the board
PD4: U41.86 (PD4); also elsewhere on the board
PD5: U41.87 (PD5); also elsewhere on the board
PD6: U41.88 (PD6); also elsewhere on the board
PD7: U41.89 (PD7); also elsewhere on the board
PE7: U41.38 (PE7); also elsewhere on the board
PF0: U41.12 (PF0); also elsewhere on the board
PF1: U41.13 (PF1); also elsewhere on the board
PF2: R166.2, U41.19 (PF2); also elsewhere on the board
PF9: U41.10 (PF9); also elsewhere on the board
PF10: R167.2, U41.11 (PF10); also elsewhere on the board
PG10: U41.14 (PG10); also elsewhere on the board
S4_RX: U41.80 (PC11); also elsewhere on the board
S4_TX: U41.79 (PC10); also elsewhere on the board
S5_RX: U41.84 (PD2); also elsewhere on the board
S5_TX: U41.81 (PC12); also elsewhere on the board
SWCLK: U41.77 (PA14); also elsewhere on the board
SWDIO: U41.76 (PA13); also elsewhere on the board
TMG_OUT1: U41.57 (PD10); also elsewhere on the board
TMG_OUT2: U41.59 (PD12); also elsewhere on the board
TMG_OUT3: U41.68 (PC9); also elsewhere on the board
TMG_OUT4: U41.61 (PD14); also elsewhere on the board
TMG_OUT5: U41.71 (PA10); also elsewhere on the board
TMG_OUT6: U41.58 (PD11); also elsewhere on the board
TMG_OUT7: U41.60 (PD13); also elsewhere on the board
TMG_OUT8: U41.62 (PD15); also elsewhere on the board
TMG_OUT9: U41.69 (PA8); also elsewhere on the board
VBUS: R145.2; also elsewhere on the board
